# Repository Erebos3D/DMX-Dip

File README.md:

# DMX-Dip
A Dip for NTCs C.H.I.P to control lights, leds and more.

For a more detailed description please visit [this forum thread](https://bbs.nextthing.co/t/yet-to-be-named-dmx-dip-control-spotlights-etc-program-lightshows-and-more/9016).  
C.H.I.P by [NTC](https://getchip.com/).

The files are KiCad files, *not EAGLE*.

---
Development for v1.0:

- Added second XLR connector  
- Transistors lay flat now  
- Improved silkscreen  
- Added header for unused atmega pins

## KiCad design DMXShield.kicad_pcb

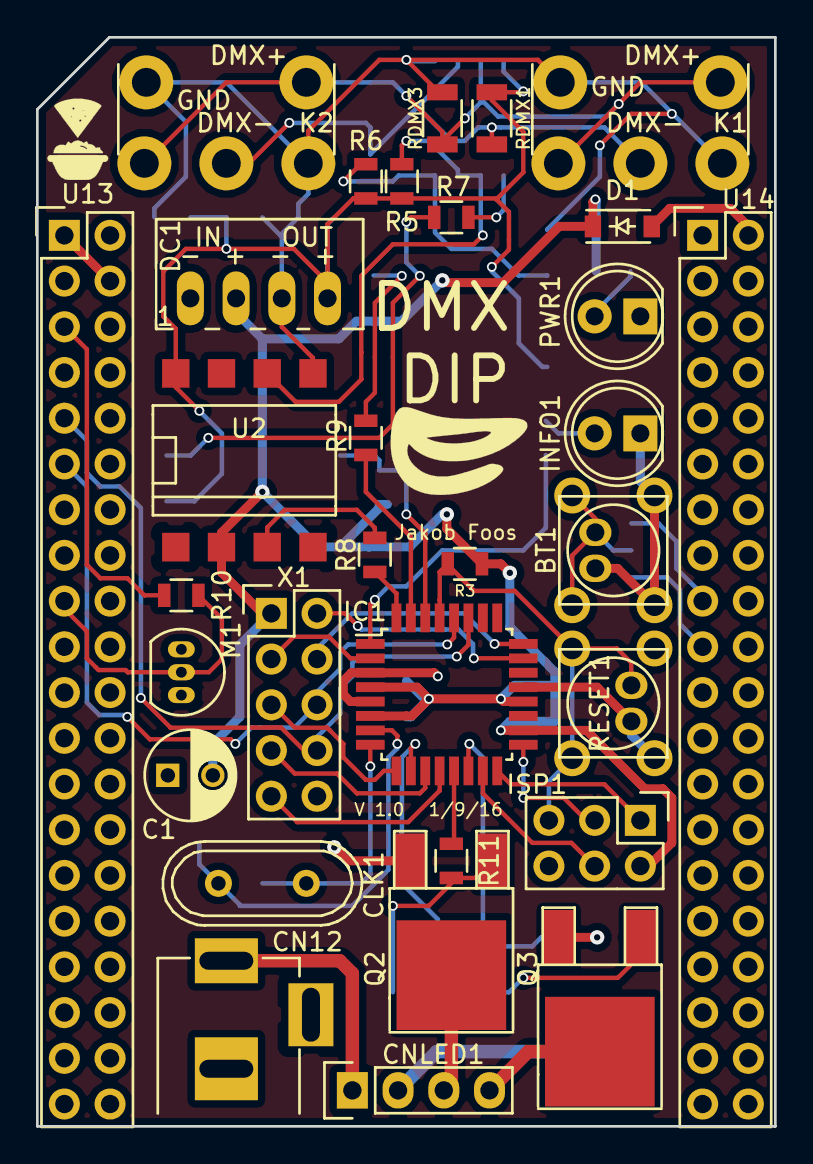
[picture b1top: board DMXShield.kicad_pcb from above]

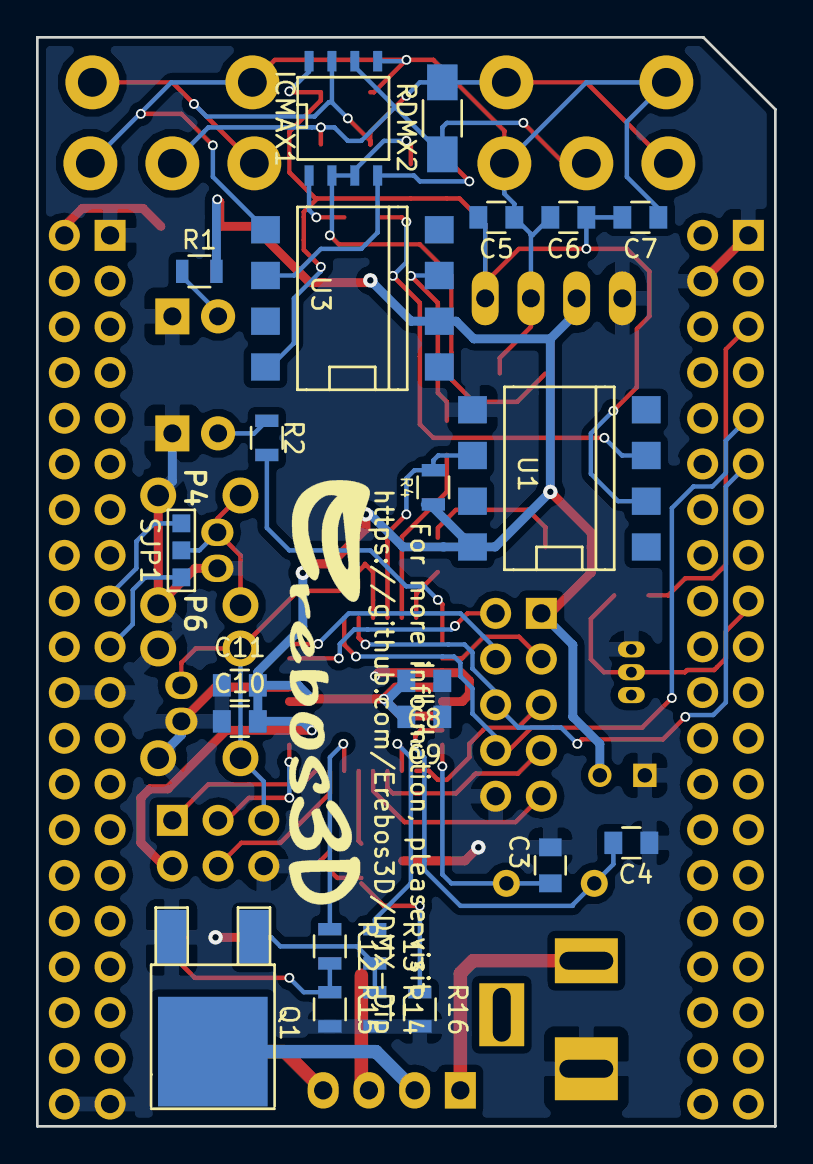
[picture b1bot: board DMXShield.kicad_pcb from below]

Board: 2 copper layers, 41.0 x 60.5 mm, 54 parts (23 on the bottom side), 48 nets.

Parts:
BT1: SW_PUSH; Switch_Plus_Connector
C1: 10u; C_Radial_D5_L11_P2.5
C3, C4: 22pF; C_0805
C5, C6, C7, C8, C9, C10, C11: 100n; C_0805
CLK1: Crystal; Crystal_HC49-U_Vertical
CN12: CONN_PWR12V; BARREL_JACK_Silk
CNLED1: 01X04; Pin_Header_Straight_1x04
D1: D_Schottky; SOD-123
DC1: AM1S_0505SZ; DCDC-Conv_TRACO_TME05xx_TME12xx
IC1: ATMEGA328P-A; TQFP-32_7x7mm_Pitch0.8mm
ICMAX1: MAX481CPA; SOIC-8-N
INFO1: LED; LED-5MM
ISP1: CONN_02X03; Pin_Header_Straight_2x03
K1, K2: XLR3; XLR_Angled_DoubleWay
M1: DS2431; TO-92_Inline_Narrow_Oval
PWR1: LED; LED-5MM
Q1, Q2, Q3: Q_NMOS_GDS; TO-252-2Lead
R1, R2: 220; R_0805
R3: 10K; R_0805
R4, R5, R6, R10, R14, R15, R16: 4K7; R_0805
R7, R8, R9: 470; R_0805
R11, R12, R13: 100; R_0805
RDMX1, RDMX3: 510; R_1206
RDMX2: 130; R_1206_HandSoldering
RESET1: SW_PUSH; Switch_Plus_Connector
SJP1: JUMPER3; Solder_Jumper_3_SMALL
U1, U2, U3: 6N136; DIP-8_SMD_Smaller
U13, U14: CONN_02X20; Pin_Header_Straight_2x20
X1: CONN_02X05; Pin_Header_Straight_2x05

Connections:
3V3: R10.1, U13.5
5V: C1.2, C8.2, C9.2, C10.2, C11.2, D1.1, DC1.2, IC1.4, IC1.6, IC1.18, IC1.20, ISP1.2, R1.2, R3.1, R4.2, U1.8, U2.2, U3.2, X1.1
5V_EXT: C5.2, C6.2, C7.2, DC1.4, ICMAX1.8, R5.2, R6.2, RDMX1.2, U1.2, U2.8, U3.8
DIRECTION: IC1.32, R8.1
GND: BT1.1, C1.1, C3.1, C4.1, C8.1, C9.1, C10.1, C11.1, CN12.1, DC1.1, IC1.3, IC1.5, IC1.21, INFO1.1, ISP1.6, M1.1, PWR1.1, Q1.3, Q2.3, Q3.3, R14.2, R15.2, R16.2, RESET1.2, U1.5, U13.1, U13.4, U13.12, U13.39, U14.1, U14.21, U14.22, U14.39, U14.40, X1.10
GND_EXT: C5.1, C6.1, C7.1, DC1.3, ICMAX1.5, K1.1, K2.1, RDMX3.1, U2.5, U3.5
INFO: IC1.1, R2.1
LCD-D2: M1.2, R10.2, U13.17
MISO: IC1.16, ISP1.1
MOSI: IC1.15, ISP1.4
unnamed: BT1.2, SJP1.2
unnamed: C3.2, CLK1.2, IC1.8
unnamed: C4.2, CLK1.1, IC1.7
unnamed: CN12.2, CNLED1.1
unnamed: CNLED1.2, Q1.2
unnamed: CNLED1.3, Q2.2
unnamed: CNLED1.4, Q3.2
unnamed: D1.2, U14.2
unnamed: IC1.10, R13.1
unnamed: IC1.13, R11.1
unnamed: IC1.14, R12.1
unnamed: ICMAX1.1, R7.2
unnamed: ICMAX1.2, ICMAX1.3, R5.1, U2.6
unnamed: ICMAX1.4, R6.1, U3.6
unnamed: ICMAX1.6, K1.2, K2.2, RDMX1.1, RDMX2.2
unnamed: ICMAX1.7, K1.3, K2.3, RDMX2.1, RDMX3.2
unnamed: INFO1.2, R2.2
unnamed: PWR1.2, R1.1
unnamed: Q1.1, R13.2, R14.1
unnamed: Q2.1, R11.2, R16.1
unnamed: Q3.1, R12.2, R15.1
unnamed: R7.1, U1.3
unnamed: R8.2, U2.3
unnamed: R9.2, U3.3
P4: SJP1.1, U14.17
P6: SJP1.3, U14.19
RESET: IC1.29, ISP1.5, R3.2, RESET1.1
RX: IC1.30, R4.1, U1.6
SCK: IC1.17, ISP1.3
TWI1-SCK: IC1.28, U13.11, X1.6
TWI1-SDA: IC1.27, U13.9, X1.8
TX: IC1.31, R9.1
X_ADC0: IC1.23, X1.2
X_ADC1: IC1.24, X1.4
X_IO0: IC1.2, X1.3
X_IO1: IC1.9, X1.5
X_IO2: IC1.11, X1.7
X_IO3: IC1.12, X1.9

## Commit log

2016-08-29 Initial commit of v0.3.
2016-09-01 First layout for V1.0
2016-09-02 Added decoupling capacitors
